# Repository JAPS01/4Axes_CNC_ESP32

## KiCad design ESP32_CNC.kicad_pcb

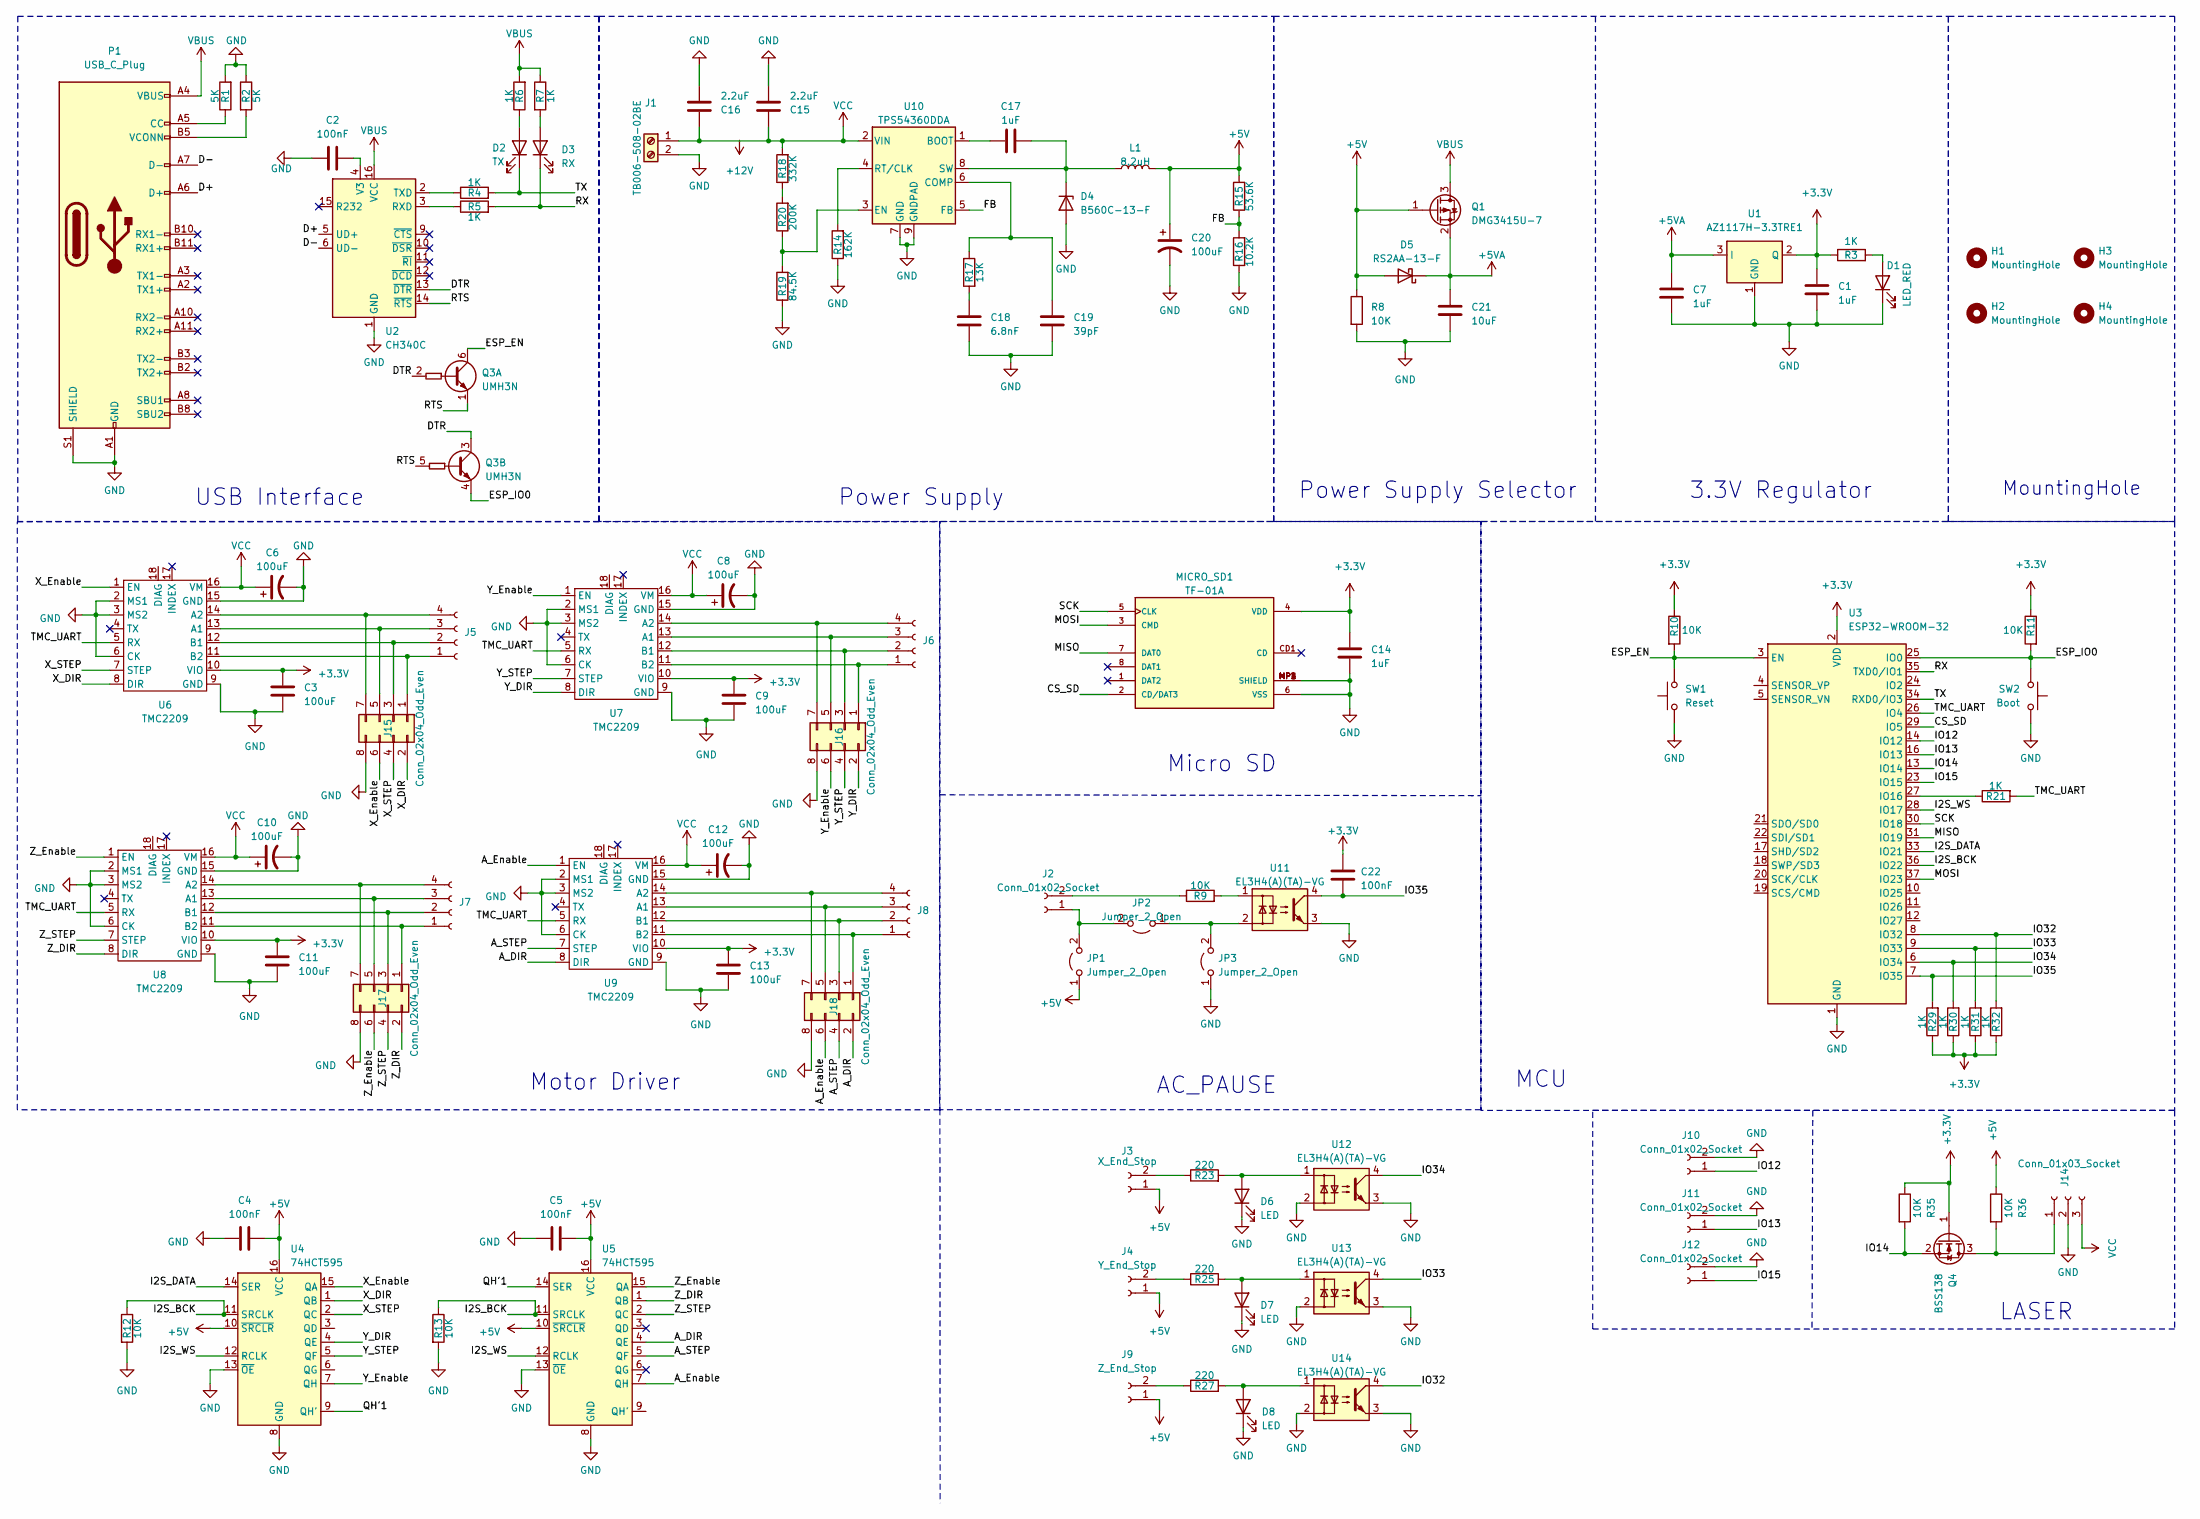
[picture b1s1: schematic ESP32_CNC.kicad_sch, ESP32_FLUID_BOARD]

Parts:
C1, C7, C14, C17: 1uF; C_1206_3216Metric_Pad1.33x1.80mm_HandSolder; LCSC C107185
C2, C4, C5, C22: 100nF; C_1206_3216Metric_Pad1.33x1.80mm_HandSolder; LCSC C82601
C3, C9, C11, C13: 100uF; C_1206_3216Metric_Pad1.33x1.80mm_HandSolder; LCSC C110048
C6, C8, C10, C12, C20: 100uF; CP_Elec_6.3x7.7; LCSC C178560
C15, C16: 2.2uF; C_1206_3216Metric_Pad1.33x1.80mm_HandSolder; LCSC C113893
C18: 6.8nF; C_1206_3216Metric_Pad1.33x1.80mm_HandSolder; LCSC C527325
C19: 39pF; C_1206_3216Metric_Pad1.33x1.80mm_HandSolder; LCSC C326958
C21: 10uF; C_1206_3216Metric_Pad1.33x1.80mm_HandSolder; LCSC C70462
D1: LED_RED; LED_1206_3216Metric_Pad1.42x1.75mm_HandSolder; LCSC C965827
D2: TX; LED_1206_3216Metric_Pad1.42x1.75mm_HandSolder; LCSC C965827
D3: RX; LED_1206_3216Metric_Pad1.42x1.75mm_HandSolder; LCSC C965827
D4: B560C-13-F; D_SMC_Handsoldering; LCSC C85100
D5: RS2AA-13-F; D_SMA
D6, D7, D8: LED; LED_1206_3216Metric_Pad1.42x1.75mm_HandSolder
H1, H2, H3, H4: MountingHole; MountingHole_2.5mm_Pad_Via
J1: TB006-508-02BE; PhoenixContact_MSTBA_2,5_2-G_1x02_P5.00mm_Horizontal; LCSC C505815
J2, J10, J11, J12: Conn_01x02_Socket; JST_XH_B2B-XH-A_1x02_P2.50mm_Vertical; LCSC C158012
J3: X_End_Stop; JST_XH_B2B-XH-A_1x02_P2.50mm_Vertical; LCSC C158012
J4: Y_End_Stop; JST_XH_B2B-XH-A_1x02_P2.50mm_Vertical; LCSC C158012
J5, J6, J7, J8: Conn_01x04_Socket; PhoenixContact_MC_1,5_4-G-3.5_1x04_P3.50mm_Horizontal; LCSC C441173
J9: Z_End_Stop; JST_XH_B2B-XH-A_1x02_P2.50mm_Vertical; LCSC C158012
J14: Conn_01x03_Socket; JST_XH_B3B-XH-A_1x03_P2.50mm_Vertical
J15, J16, J17, J18: Conn_02x04_Odd_Even; PinHeader_2x04_P2.54mm_Vertical
JP1, JP2, JP3: Jumper_2_Open; SolderJumper-2_P1.3mm_Open_RoundedPad1.0x1.5mm
L1: 8.2uH; L_Chilisin_BMRx00060630; LCSC C5349707
MICRO_SD1: TF-01A; LCSC C91145
P1: USB_C_Plug; USB_C_Receptacle_XKB_U262-16XN-4BVC11; LCSC C319148
Q1: DMG3415U-7; SOT-23; LCSC C96616
Q3: UMH3N; SOT-363_SC-70-6; LCSC C62892
Q4: BSS138; SOT-23
R1, R2: 5K; R_1206_3216Metric_Pad1.30x1.75mm_HandSolder; LCSC C870818
R3, R4, R5, R6, R7, R21, R29, R30, R31, R32: 1K; R_1206_3216Metric_Pad1.30x1.75mm_HandSolder; LCSC C112223
R8, R10, R11, R12, R13, R35, R36: 10K; R_1206_3216Metric_Pad1.30x1.75mm_HandSolder; LCSC C132649
R9: 10K; R_1206_3216Metric_Pad1.30x1.75mm_HandSolder
R14: 162K; R_1206_3216Metric_Pad1.30x1.75mm_HandSolder; LCSC C229338
R15: 53.6K; R_1206_3216Metric_Pad1.30x1.75mm_HandSolder; LCSC C229697
R16: 10.2K; R_1206_3216Metric_Pad1.30x1.75mm_HandSolder; LCSC C229274
R17: 13K; R_1206_3216Metric_Pad1.30x1.75mm_HandSolder; LCSC C229313
R18: 332K; R_1206_3216Metric_Pad1.30x1.75mm_HandSolder; LCSC C229555
R19: 84.5K; R_1206_3216Metric_Pad1.30x1.75mm_HandSolder; LCSC C229820
R20: 200K; R_1206_3216Metric_Pad1.30x1.75mm_HandSolder; LCSC C114937
R23, R25, R27: 220; R_1206_3216Metric_Pad1.30x1.75mm_HandSolder; LCSC C137176
SW1: Reset; JT1140; LCSC C465061
SW2: Boot; JT1140; LCSC C465061
U1: AZ1117H-3.3TRE1; SOT-223; LCSC C92517
U2: CH340C; SOIC-16_3.9x9.9mm_P1.27mm; LCSC C84681
U3: ESP32-WROOM-32
U4, U5: 74HCT595; TSSOP-16_4.4x5mm_P0.65mm; LCSC C842461
U6, U7, U8, U9: TMC2209
U10: TPS54360DDA; TI_SO-PowerPAD-8_ThermalVias; LCSC C44377
U11, U12, U13, U14: EL3H4(A)(TA)-VG; SOP-4_4.4x2.6mm_P1.27mm; LCSC C142289

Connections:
+3.3V: C1.1, C3.2, C9.2, C11.2, C13.2, C14.1, C22.2, MICRO_SD1.4 (VDD), Q4.1 (G), R3.1, R10.1, R11.1, R29.1, R30.1, R31.1, R32.1, R35.1, U1.2 (Q), U3.2 (VDD), U6.10 (VIO), U7.10 (VIO), U8.10 (VIO), U9.10 (VIO)
+5V: C4.2, C5.2, C20.1, D5.2 (A), J3.1, J4.1, J9.1, JP1.1 (A), L1.2, Q1.1 (G), R8.1, R15.2, R36.1, U4.10 (~SRCLR), U4.16 (VCC), U5.10 (~SRCLR), U5.16 (VCC)
+5VA: C7.1, C21.1, D5.1 (K), Q1.2 (S), U1.3 (I)
/A_DIR: J18.2, U5.4 (QE), U9.8 (DIR)
/A_Enable: J18.6, U5.7 (QH), U9.1 (EN)
/A_STEP: J18.4, U5.5 (QF), U9.7 (STEP)
/CS_SD: MICRO_SD1.2 (CD/DAT3), U3.29 (IO5)
/D+: P1.A6 (D+), U2.5 (UD+)
/D-: P1.A7 (D-), U2.6 (UD-)
/DTR: Q3.2 (B1), Q3.3 (C2), U2.13 (~DTR)
/ESP_EN: Q3.6 (C1), R10.2, SW1.2, U3.3 (EN)
/ESP_IO0: Q3.4 (E2), R11.2, SW2.2, U3.25 (IO0)
/FB: R15.1, R16.2, U10.5 (FB)
/I2S_BCK: R12.1, R13.1, U3.36 (IO22), U4.11 (SRCLK), U5.11 (SRCLK)
/I2S_DATA: U3.33 (IO21), U4.14 (SER)
/I2S_WS: U3.28 (IO17), U4.12 (RCLK), U5.12 (RCLK)
/IO12: J10.1, U3.14 (IO12)
/IO13: J11.1, U3.16 (IO13)
/IO14: Q4.2 (S), R35.2, U3.13 (IO14)
/IO15: J12.1, U3.23 (IO15)
/IO32: R32.2, U3.8 (IO32), U14.4
/IO33: R31.2, U3.9 (IO33), U13.4
/IO34: R30.2, U3.6 (IO34), U12.4
/IO35: C22.1, R29.2, U3.7 (IO35), U11.4
/MISO: MICRO_SD1.7 (DAT0), U3.31 (IO19)
/MOSI: MICRO_SD1.3 (CMD), U3.37 (IO23)
/QH'1: U4.9 (QH'), U5.14 (SER)
/RTS: Q3.1 (E1), Q3.5 (B2), U2.14 (~RTS)
/RX: D3.1 (K), R5.2, U3.35 (TXD0/IO1)
/SCK: MICRO_SD1.5 (CLK), U3.30 (IO18)
/TMC_UART: R21.2, U3.26 (IO4), U6.5 (RX), U7.5 (RX), U8.5 (RX), U9.5 (RX)
/TX: D2.1 (K), R4.2, U3.34 (RXD0/IO3)
/X_DIR: J15.2, U4.1 (QB), U6.8 (DIR)
/X_Enable: J15.6, U4.15 (QA), U6.1 (EN)
/X_STEP: J15.4, U4.2 (QC), U6.7 (STEP)
/Y_DIR: J16.2, U4.4 (QE), U7.8 (DIR)
/Y_Enable: J16.6, U4.7 (QH), U7.1 (EN)
/Y_STEP: J16.4, U4.5 (QF), U7.7 (STEP)
/Z_DIR: J17.2, U5.1 (QB), U8.8 (DIR)
/Z_Enable: J17.6, U5.15 (QA), U8.1 (EN)
/Z_STEP: J17.4, U5.2 (QC), U8.7 (STEP)
GND: C1.2, C2.1, C3.1, C4.1, C5.1, C6.2, C7.2, C8.2, C9.1, C10.2, C11.1, C12.2, C13.1, C14.2, C15.2, C16.2, C18.2, C19.1, C20.2, C21.2, D1.1 (K), D4.2 (A), D6.1 (K), D7.1 (K), D8.1 (K), J1.2, J10.2, J11.2, J12.2, J14.2, J15.8, J16.8, J17.8, J18.8, JP3.1 (A), MICRO_SD1.6 (VSS), MICRO_SD1.MP1 (SHIELD), MICRO_SD1.MP2 (SHIELD), MICRO_SD1.MP3 (SHIELD), MICRO_SD1.MP4 (SHIELD), P1.A1 (GND), P1.A12 (GND), P1.B1 (GND), P1.B12 (GND), P1.S1 (SHIELD), R1.2, R2.1, R8.2, R12.2, R13.2, R14.1, R16.1, R19.1, SW1.1, SW2.1, U1.1 (GND), U2.1 (GND), U3.1 (GND), U3.15 (GND), U3.38 (GND), U3.39 (GND), U4.8 (GND), U4.13 (~OE), U5.8 (GND), U5.13 (~OE), U6.2 (MS1), U6.3 (MS2), U6.6 (CK), U6.9 (GND), U6.15 (GND), U7.2 (MS1), U7.3 (MS2), U7.6 (CK), U7.9 (GND), U7.15 (GND), U8.2 (MS1), U8.3 (MS2), U8.6 (CK), U8.9 (GND), U8.15 (GND), U9.2 (MS1), U9.3 (MS2), U9.6 (CK), U9.9 (GND), U9.15 (GND), U10.7 (GND), U10.9 (GNDPAD), U11.3, U12.2, U12.3, U13.2, U13.3, U14.2, U14.3
unnamed: C18.1, R17.2
unnamed: D1.2 (A), R3.2
unnamed: D2.2 (A), R6.1
unnamed: D3.2 (A), R7.2
unnamed: C17.2, D4.1 (K), L1.1, U10.8 (SW)
unnamed: D6.2 (A), R23.2, U12.1
unnamed: D7.2 (A), R25.2, U13.1
unnamed: D8.2 (A), R27.2, U14.1
unnamed: J2.1, JP1.2 (B), JP2.2 (B)
unnamed: J2.2, R9.1
unnamed: J3.2, R23.1
unnamed: J4.2, R25.1
unnamed: J9.2, R27.1
unnamed: J14.1, Q4.3 (D), R36.2
unnamed: J5.1, J15.1, U6.11 (B2)
unnamed: J5.2, J15.3, U6.12 (B1)
unnamed: J5.3, J15.5, U6.13 (A1)
unnamed: J5.4, J15.7, U6.14 (A2)
unnamed: J6.1, J16.1, U7.11 (B2)
unnamed: J6.2, J16.3, U7.12 (B1)
unnamed: J6.3, J16.5, U7.13 (A1)
unnamed: J6.4, J16.7, U7.14 (A2)
unnamed: J7.1, J17.1, U8.11 (B2)
unnamed: J7.2, J17.3, U8.12 (B1)
unnamed: J7.3, J17.5, U8.13 (A1)
unnamed: J7.4, J17.7, U8.14 (A2)
unnamed: J8.1, J18.1, U9.11 (B2)
unnamed: J8.2, J18.3, U9.12 (B1)
unnamed: J8.3, J18.5, U9.13 (A1)
unnamed: J8.4, J18.7, U9.14 (A2)
unnamed: JP2.1 (A), JP3.2 (B), U11.2
unnamed: P1.A5 (CC), R1.1
unnamed: P1.B5 (VCONN), R2.2
unnamed: R9.2, U11.1
unnamed: R18.1, R20.2
unnamed: R5.1, U2.3 (RXD)
unnamed: R4.1, U2.2 (TXD)
unnamed: C2.2, U2.4 (V3)
unnamed: R21.1, U3.27 (IO16)
unnamed: C17.1, U10.1 (BOOT)
unnamed: C19.2, R17.1, U10.6 (COMP)
unnamed: R19.2, R20.1, U10.3 (EN)
unnamed: R14.2, U10.4 (RT/CLK)
VBUS: P1.A4 (VBUS), P1.A9 (VBUS), P1.B4 (VBUS), P1.B9 (VBUS), Q1.3 (D), R6.2, R7.1, U2.16 (VCC)
VCC: C6.1, C8.1, C10.1, C12.1, C15.1, C16.1, J1.1, J14.3, R18.2, U6.16 (VM), U7.16 (VM), U8.16 (VM), U9.16 (VM), U10.2 (VIN)

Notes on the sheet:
MCU
Motor Driver
AC_PAUSE
USB Interface
Micro SD
LASER
MountingHole
3.3V Regulator
Power Supply
Power Supply Selector

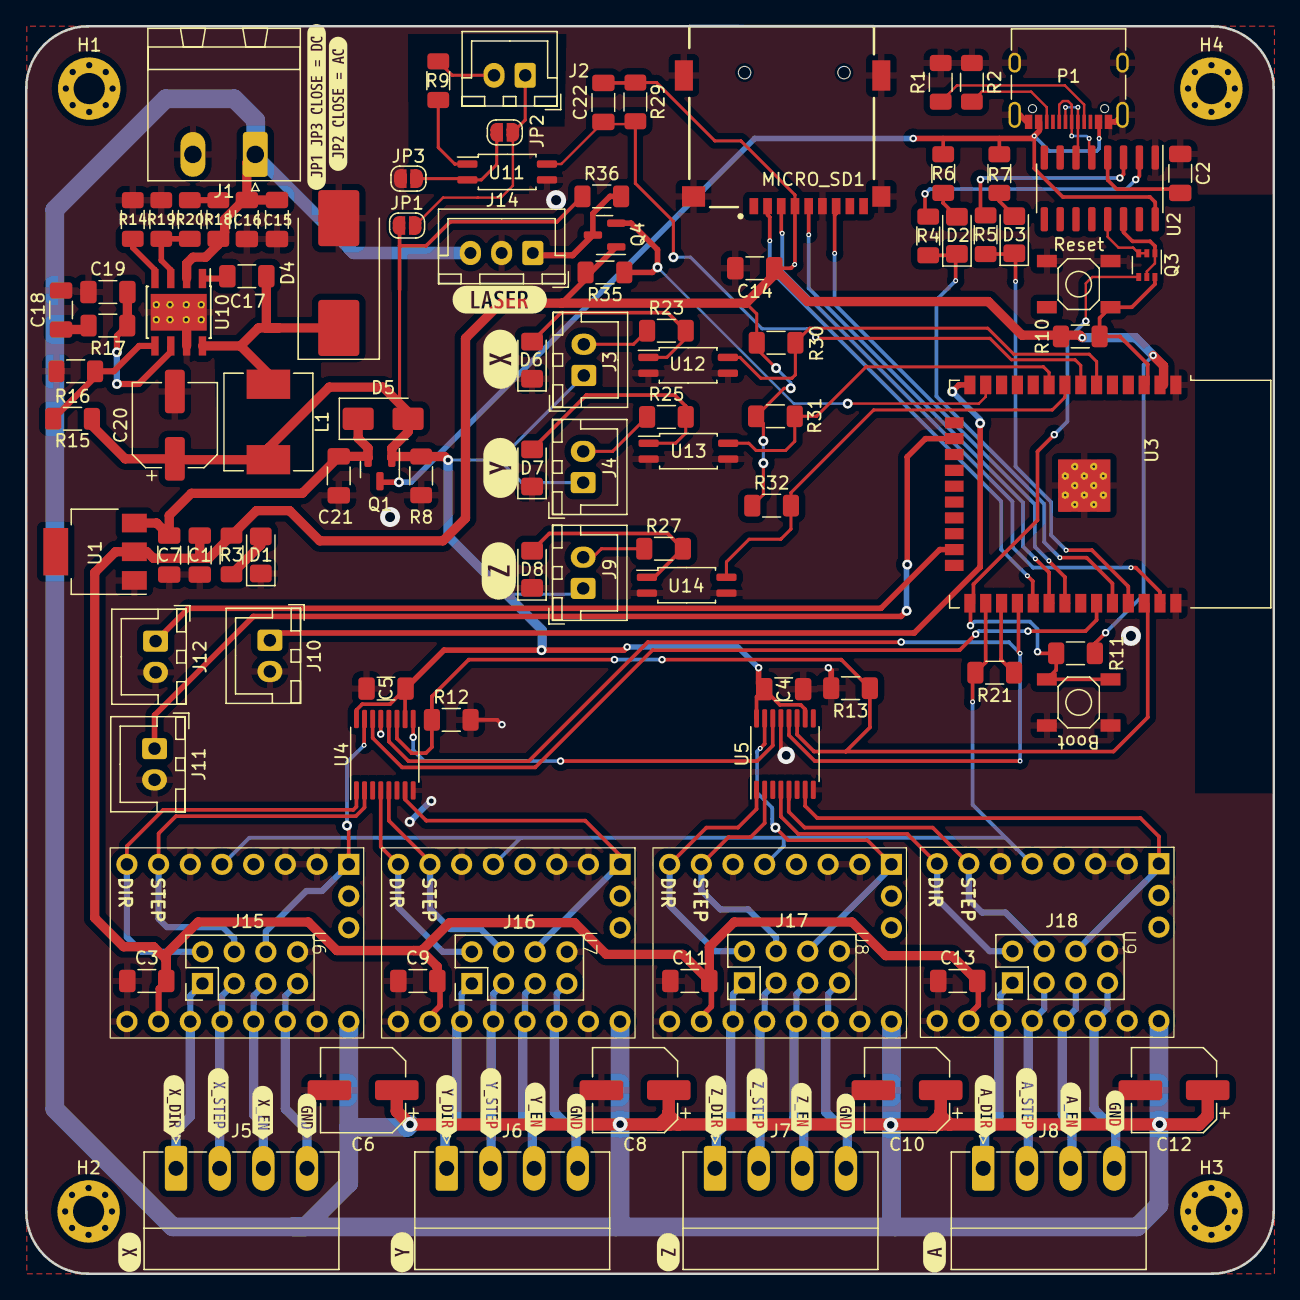
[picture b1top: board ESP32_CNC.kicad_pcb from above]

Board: 2 copper layers, 100.0 x 100.0 mm, 132 parts (0 on the bottom side), 87 nets.

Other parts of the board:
kibuzzard-64A8D498: G***; kibuzzard-64A8D498
kibuzzard-64A9FD55: G***; kibuzzard-64A9FD55
kibuzzard-64A9FD75: G***; kibuzzard-64A9FD75
kibuzzard-64AA0C0E: G***; kibuzzard-64AA0C0E
kibuzzard-64AA0C1E: G***; kibuzzard-64AA0C1E
kibuzzard-64AA0C27: G***; kibuzzard-64AA0C27
kibuzzard-64AA3047: G***; kibuzzard-64AA3047
kibuzzard-64AF2DE8: G***; kibuzzard-64AF2DE8
kibuzzard-64AF2E2C: G***; kibuzzard-64AF2E2C
kibuzzard-64AF2E5B: G***; kibuzzard-64AF2E5B
kibuzzard-64AF2E13: G***; kibuzzard-64AF2E13
kibuzzard-64AF2E33, kibuzzard-64AF2E33#2, kibuzzard-64AF2E33#3, kibuzzard-64AF2E33#4: G***; kibuzzard-64AF2E33
kibuzzard-64AF2E65: G***; kibuzzard-64AF2E65
kibuzzard-64AF2EE8: G***; kibuzzard-64AF2EE8
kibuzzard-64AF2EF3: G***; kibuzzard-64AF2EF3
kibuzzard-64AF2EFB: G***; kibuzzard-64AF2EFB
kibuzzard-64AF2F0A: G***; kibuzzard-64AF2F0A
kibuzzard-64AF2F1D: G***; kibuzzard-64AF2F1D
kibuzzard-64AF2F02: G***; kibuzzard-64AF2F02
kibuzzard-64AF2F11: G***; kibuzzard-64AF2F11
kibuzzard-64AF2FB1: G***; kibuzzard-64AF2FB1
kibuzzard-64AF2FF1: G***; kibuzzard-64AF2FF1
kibuzzard-64AF3027: G***; kibuzzard-64AF3027

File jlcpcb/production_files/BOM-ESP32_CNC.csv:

Comment,Designator,Footprint,LCSC
1uF,"C1,C14,C17,C7",C_1206_3216Metric_Pad1.33x1.80mm_HandSolder,C107185
100uF,"C11,C13,C3,C9",C_1206_3216Metric_Pad1.33x1.80mm_HandSolder,C110048
1K,"R21,R29,R3,R30,R31,R32,R4,R5,R6,R7",R_1206_3216Metric_Pad1.30x1.75mm_HandSolder,C112223
2.2uF,"C15,C16",C_1206_3216Metric_Pad1.33x1.80mm_HandSolder,C113893
200K,R20,R_1206_3216Metric_Pad1.30x1.75mm_HandSolder,C114937
10K,"R10,R11,R12,R13,R35,R36,R8",R_1206_3216Metric_Pad1.30x1.75mm_HandSolder,C132649
220,"R23,R25,R27",R_1206_3216Metric_Pad1.30x1.75mm_HandSolder,C137176
EL3H4(A)(TA)-VG,"U11,U12,U13,U14",SOP-4_4.4x2.6mm_P1.27mm,C142289
Conn_01x02_Socket,"J10,J11,J12,J2,J3,J4,J9",JST_XH_B2B-XH-A_1x02_P2.50mm_Vertical,C158012
100uF,"C10,C12,C20,C6,C8",CP_Elec_6.3x7.7,C178560
10.2K,R16,R_1206_3216Metric_Pad1.30x1.75mm_HandSolder,C229274
13K,R17,R_1206_3216Metric_Pad1.30x1.75mm_HandSolder,C229313
162K,R14,R_1206_3216Metric_Pad1.30x1.75mm_HandSolder,C229338
332K,R18,R_1206_3216Metric_Pad1.30x1.75mm_HandSolder,C229555
53.6K,R15,R_1206_3216Metric_Pad1.30x1.75mm_HandSolder,C229697
84.5K,R19,R_1206_3216Metric_Pad1.30x1.75mm_HandSolder,C229820
USB_C_Plug,P1,USB_C_Receptacle_XKB_U262-16XN-4BVC11,C319148
39pF,C19,C_1206_3216Metric_Pad1.33x1.80mm_HandSolder,C326958
Conn_01x04_Socket,"J5,J6,J7,J8","PhoenixContact_MC_1,5_4-G-3.5_1x04_P3.50mm_Horizontal",C441173
TPS54360DDA,U10,TI_SO-PowerPAD-8_ThermalVias,C44377
Reset,"SW1,SW2",JT1140,C465061
TB006-508-02BE,J1,"PhoenixContact_MSTBA_2,5_2-G_1x02_P5.00mm_Horizontal",C505815
6.8nF,C18,C_1206_3216Metric_Pad1.33x1.80mm_HandSolder,C527325
8.2uH,L1,L_Chilisin_BMRx00060630,C5349707
UMH3N,Q3,SOT-363_SC-70-6,C62892
10uF,C21,C_1206_3216Metric_Pad1.33x1.80mm_HandSolder,C70462
100nF,"C2,C22,C4,C5",C_1206_3216Metric_Pad1.33x1.80mm_HandSolder,C82601
74HCT595,"U4,U5",TSSOP-16_4.4x5mm_P0.65mm,C842461
CH340C,U2,SOIC-16_3.9x9.9mm_P1.27mm,C84681
B560C-13-F,D4,D_SMC_Handsoldering,C85100
5K,"R1,R2",R_1206_3216Metric_Pad1.30x1.75mm_HandSolder,C870818
TF-01A,MICRO_SD1,TF-01A,C91145
AZ1117H-3.3TRE1,U1,SOT-223,C92517
LED_RED,"D1,D2,D3",LED_1206_3216Metric_Pad1.42x1.75mm_HandSolder,C965827
DMG3415U-7,Q1,SOT-23,C96616
ESP32-WROOM-32,U3,ESP32-WROOM-32,
MountingHole,H4,MountingHole_2.5mm_Pad_Via,
MountingHole,H3,MountingHole_2.5mm_Pad_Via,
MountingHole,H2,MountingHole_2.5mm_Pad_Via,
MountingHole,H1,MountingHole_2.5mm_Pad_Via,
TMC2209,U9,TMC2209,
TMC2209,U6,TMC2209,
TMC2209,U7,TMC2209,
TMC2209,U8,TMC2209,
RS2AA-13-F,D5,D_SMA,
Jumper_2_Open,JP3,SolderJumper-2_P1.3mm_Open_RoundedPad1.0x1.5mm,
Jumper_2_Open,JP2,SolderJumper-2_P1.3mm_Open_RoundedPad1.0x1.5mm,
Jumper_2_Open,JP1,SolderJumper-2_P1.3mm_Open_RoundedPad1.0x1.5mm,
10K,R9,R_1206_3216Metric_Pad1.30x1.75mm_HandSolder,
Conn_01x03_Socket,J14,JST_XH_B3B-XH-A_1x03_P2.50mm_Vertical,
Conn_02x04_Odd_Even,J18,PinHeader_2x04_P2.54mm_Vertical,
Conn_02x04_Odd_Even,J17,PinHeader_2x04_P2.54mm_Vertical,
Conn_02x04_Odd_Even,J16,PinHeader_2x04_P2.54mm_Vertical,
Conn_02x04_Odd_Even,J15,PinHeader_2x04_P2.54mm_Vertical,
BSS138,Q4,SOT-23,
LED,D7,LED_1206_3216Metric_Pad1.42x1.75mm_HandSolder,
LED,D8,LED_1206_3216Metric_Pad1.42x1.75mm_HandSolder,
LED,D6,LED_1206_3216Metric_Pad1.42x1.75mm_HandSolder,

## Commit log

2023-11-01 Rev 1
